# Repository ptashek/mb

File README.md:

Various projects related to vintage Merceses-Benz vehicles, mostly the W116 series.

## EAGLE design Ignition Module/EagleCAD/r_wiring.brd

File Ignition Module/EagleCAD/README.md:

W116 V8 ignition module
Reverse engineered from Bosch part number 0227100001B

*NOTE:* None of the drawings, designs or other details in this project can be used for commercial purposes.

Contents:
- datasheets for all relevant elements
- component libraries for EagleCAD
- scope traces from a prototype module used to verify the design
- EagleCAD schematic + base board layout

Short video of a fully working prototype:
https://www.youtube.com/watch?v=qzFwiPDNBnE

Original and prototype module debugging:
http://www.dropbox.com/s/egofnxogmlrx4nw/IMG_20150903_230016.jpg
http://www.dropbox.com/s/80sc3pxkkf98rzw/IMG_20150903_225421.jpg

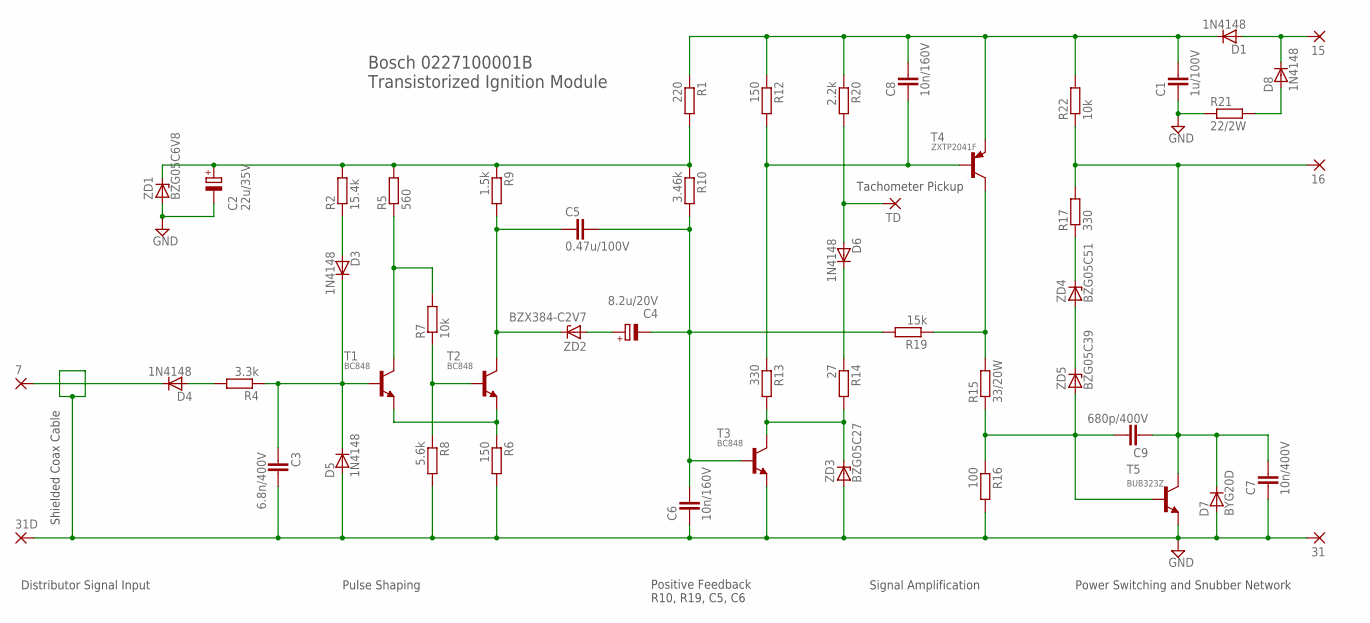
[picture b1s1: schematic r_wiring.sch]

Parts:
7, 15, 16, 31, 31D: WIREPADSMD5-2,5; 5-2,5
C1: 1u/100V; C1206
C2: 22u/35V; PANASONIC_G
C3: 6.8n/400V; C1206
C4: 8.2u/20V; PANASONIC_G
C5: 0.47u/100V; C1206
C6, C8: 10n/160V; C1206
C7: 10n/400V; C1206
C9: 680p/400V; C1206
D1, D3, D4, D5, D6, D8: 1N4148; SOD123
D7: BYG20D; DO214AC
R1: 220; R2512
R2: 15.4k; R2512
R4: 3.3k; R2512
R5: 560; R2512
R6, R12: 150; R2512
R7, R22: 10k; R2512
R8: 5.6k; R2512
R9: 1.5k; R2512
R10: 3.46k; R2512
R13, R17: 330; R2512
R14: 27; R2512
R15: 33/20W; DPAK; VOLTAGE_RATING >=200V DC
R16: 100; R2512
R19: 15k; R2512
R20: 2.2k; R2512
R21: 22/2W; R2512
T1, T2, T3: BC848; SOT23
T4: ZXTP2041F; SOT23-BCE
T5: BUB323Z; DPAK
TD: WIREPADSMD5-2,5; 5-2,5
ZD1: BZG05C6V8; SMB
ZD2: BZX384-C2V7; SOD-323F
ZD3: BZG05C27; SMB
ZD4: BZG05C51; SMB
ZD5: BZG05C39; SMB

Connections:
GND: 31.1, 31D.1, C1.2, C2.-, C3.1, C6.2, C7.2, D5.A, D7.A, R6.2, R8.2, R16.2, R21.1, T3.2 (E), T5.3 (E), ZD1.A, ZD3.A
unnamed: 7.1, D4.C
unnamed: D4.A, R4.2
unnamed: C3.2, D3.C, D5.C, R4.1, T1.1 (B)
unnamed: R6.1, T1.2 (E), T2.2 (E)
unnamed: R7.1, R8.1, T2.1 (B)
unnamed: R5.1, R7.2, T1.3 (C)
unnamed: C2.+, R1.2, R2.2, R5.2, R9.1, R10.1, ZD1.C
unnamed: C4.+, ZD2.A
unnamed: D3.A, R2.1
unnamed: C5.2, R9.2, T2.3 (C), ZD2.C
unnamed: C4.-, C5.1, C6.1, R10.2, R19.2, T3.1 (B)
unnamed: R15.3 (2), R19.1, T4.C
unnamed: C1.1, C8.1, D1.C, R1.1, R12.1, R20.1, R22.2, T4.E
unnamed: D6.A, R20.2, TD.1
unnamed: C8.2, R12.2, R13.1, T4.B
unnamed: D6.C, R14.1
unnamed: 15.1, D1.A, D8.C
unnamed: D8.A, R21.2
unnamed: R17.1, ZD4.C
unnamed: 16.1, C7.1, C9.2, D7.C, R17.2, R22.1, T5.4 (C)
unnamed: ZD4.A, ZD5.C
unnamed: C9.1, R15.1, R16.1, T5.1 (B), ZD5.A
unnamed: R13.2, R14.2, T3.3 (C), ZD3.C

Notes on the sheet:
Shielded Coax Cable
Tachometer Pickup
Distributor Signal Input
Pulse Shaping
Power Switching and Snubber Network
Signal Amplification
Positive Feedback R10, R19, C5, C6
Bosch 0227100001B Transistorized Ignition Module

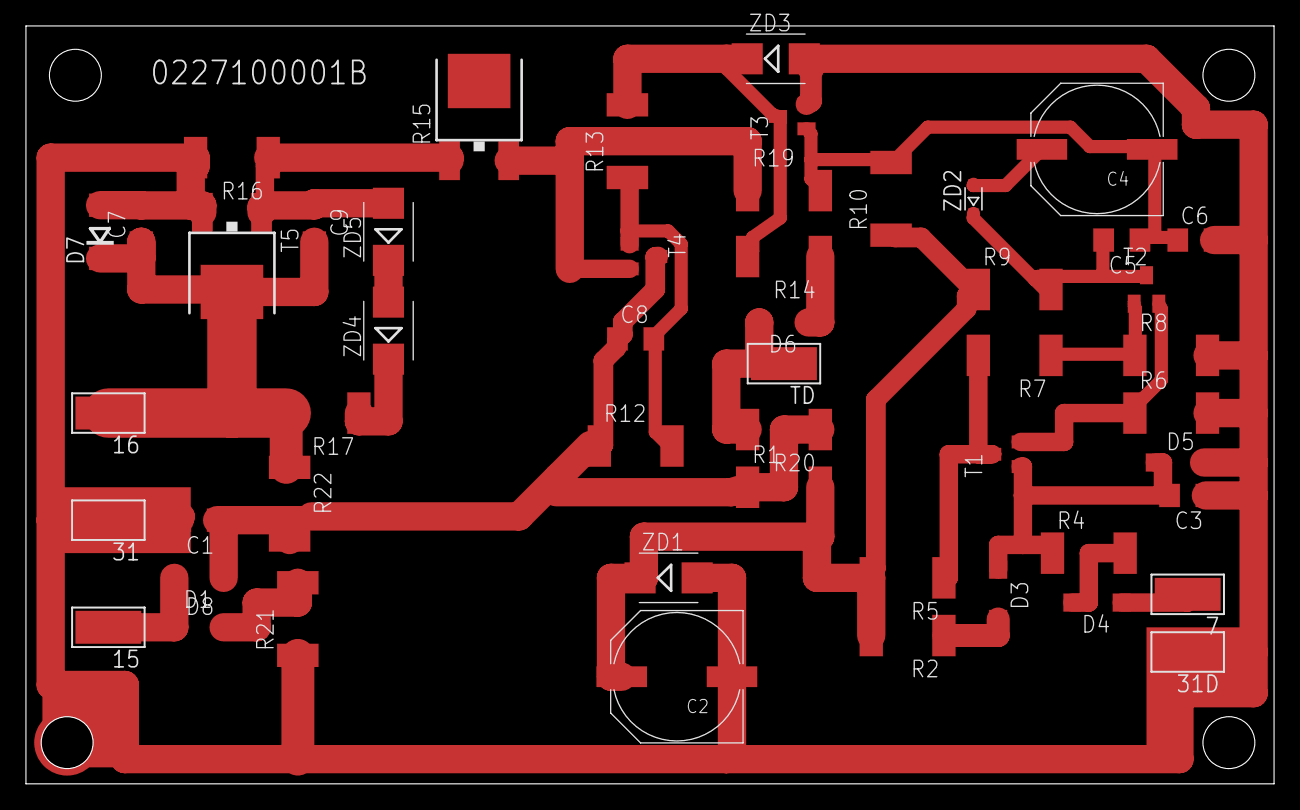
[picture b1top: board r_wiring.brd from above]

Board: 2 copper layers, 96.2 x 58.4 mm, 51 parts (0 on the bottom side), 24 nets.

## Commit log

2015-09-09 Updated READM for ignition module
2015-09-12 Updated board layout and routing
2015-09-13 Circuit and board updates
    Updated circuit with functional layout and annotations. Revised and
    added component ratings. Added BOM. Updated board layout. Updates
    provided by djenka018 of http://forum.w116.org
2015-09-17 Ignition Module Box 3D model
    First, yet unverified, 3D reproduction of the ignition module box.
    Box, seal, lid and bolts. No main connector and its seal yet.
    Autodesk Inventor 2014 format.
2015-09-19 Box model + assembly
    * Final box model verified with test 3D print
    * Test connector model (unfinished)
    * STL exports for all parts
    * Autodesk Inventor assembly file
    TODO:
    Finalize connector
2015-09-21 Updated model
    * Added mount holes for PCB platform (needs drawing)
    * Updated drill holes to M4 normal-fit drill size
    * Finished connector assembly
2015-10-09 Updates to 3D models
    - cruise control actuator cable parts updated/revised/added
    - updated ignition module box parts
2015-12-30 Crude reproduction of A1165450700
    Not aiming to be 100% perfect here. This part is available, and cheap,
    from Mercedes-Benz as of 12/2015. You should aim to buy the original,
    and use this reproduction as a backup.
2016-03-28 Fix missing net
    + Fix missing net T5.B -> R15:R16
    + Rename C8 <-> C9
    + Replace D8 with 1N4148
    + Replace parallel R2 (24k) + R3 (41.2k) with 15.4k R2 only
    + Update PCB layout + routing
2021-04-05 Add W124 cruise control project files
2021-04-05 Change README
2021-04-05 Add W124 cruise control project files (#2)
2021-04-05 CC enabled check removed from pidSwitchToAuto
2021-04-05 CC enabled check removed from pidSwitchToAuto (#3)
2021-04-21 Code revision 2 + updated README
2021-04-28 Final speed loop tuning, input filtering added
2021-05-23 Updated README and Revision 3 schematic
2021-07-05 Hall sensor reference data
2021-07-05 Hall sensor reference data (#4)
2021-07-05 Update README.md
    Updated speed sensor section based on further research and testing.
2021-07-05 Update README.md (#5)
    Updated speed sensor section based on further research and testing.
